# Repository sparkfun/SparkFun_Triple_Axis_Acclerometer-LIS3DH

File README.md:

SparkFun Triple Axis Accelerometer Breakout - LIS3DH (Qwiic)
========================================

<table class="table table-hover table-striped table-bordered">
  <tr align="center">
   <td></td> 
   <td></td>
  </tr>
  <tr align="center">
    <td><a href="https://www.sparkfun.com/sparkfun-triple-axis-accelerometer-breakout-lis3dh.html">SparkFun Triple Axis Accelerometer Breakout - LIS3DH (Qwiic) <br />(SEN-29528)</a></td>
    <td><a href="https://www.sparkfun.com/sparkfun-micro-triple-axis-accelerometer-breakout-lis3dh.html">SparkFun Micro Triple Axis Accelerometer Breakout - LIS3DH (Qwiic) <br />(SEN-29529)</a></td>
  </tr>
</table>

The SparkFun Triple Axis Accelerometer Breakout - LIS3DH (Qwiic) and SparkFun Micro Triple Axis Accelerometer Breakout - LIS3DH (Qwiic) are Qwiic breakouts for the LIS3DH from STMicroelectronics<sup>&trade;</sup>. The LIS3DH is a smart, low-power, three-axis, capacitive micro-machined accelerometer with 12 bits of resolution that you can use to add translation detection to your project. These Qwiic breakouts let users easily and solderlessly integrate a precise 3-axis accelerometer into their project.

Repository Contents
-------------------

* **/Documentation** - Data sheets, additional product information
* **/Hardware** - Eagle design files (.brd, .sch)
* **/Production** - Production panel files (.brd)

Documentation
--------------
* **[Arduino Library](https://github.com/sparkfun/SparkFun_LIS3DH_Arduino_Library)** - Arduino library for the SparkFun LIS3DH Breakouts.
* **[Hookup Guide](https://learn.sparkfun.com/tutorials/lis3dh-hookup-guide)** - Basic hookup guide for the SparkFun LIS3DH Breakouts.

Product Versions
----------------
* [SEN-29528](https://www.sparkfun.com/sparkfun-triple-axis-accelerometer-breakout-lis3dh.html) - Standard 1"x1" Qwiic Breakout
* [SEN-29529](https://www.sparkfun.com/sparkfun-micro-triple-axis-accelerometer-breakout-lis3dh.html) - Micro Qwiic Breakout

License Information
-------------------

This product is _**open source**_! 

Please review the LICENSE.md file for license information. 

If you have any questions or concerns on licensing, please contact technical support on our [SparkFun forums](https://forum.sparkfun.com/viewforum.php?f=152).

Distributed as-is; no warranty is given.

- Your friends at SparkFun.

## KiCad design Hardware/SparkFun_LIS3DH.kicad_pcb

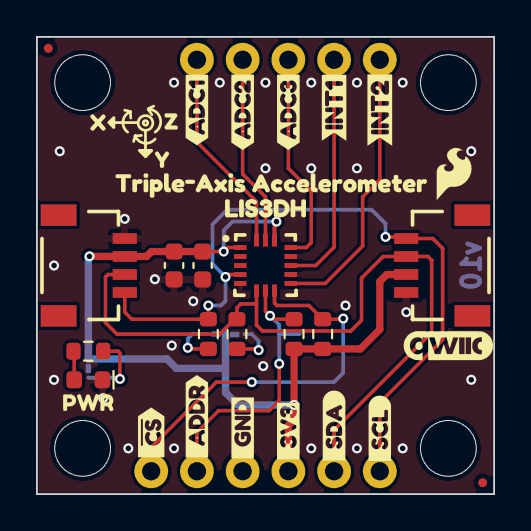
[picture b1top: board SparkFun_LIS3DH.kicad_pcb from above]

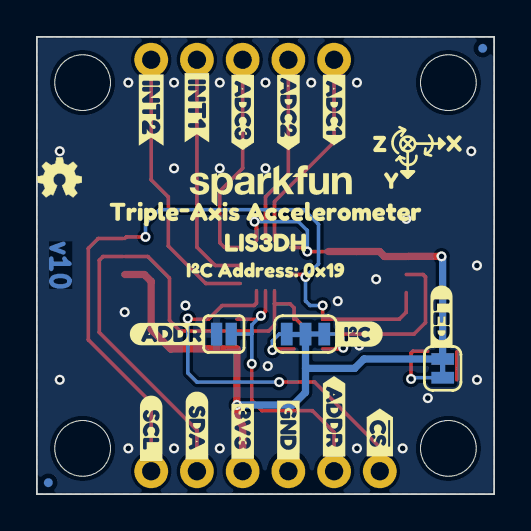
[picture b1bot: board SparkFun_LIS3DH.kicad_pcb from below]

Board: 2 copper layers, 25.4 x 25.4 mm, 64 parts (26 on the bottom side), 15 nets.

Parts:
C1: 10uF; C_0603_1608Metric
C2: 0.1uF; C_0603_1608Metric
D1: Red; LED_0603_1608Metric_Red
FID1, FID2, FID3, FID4: Fiducial_0.5mm; Fiducial_0.5mm_Mask1mm
G4: OSHW_Logo; Creative_Commons_License
J1: Conn_01x02; 1x02
J2: Conn_01x05; 1x05
J3, J5: Qwiic_RA; JST_SMD_1.0mm-4_Black
J4: I2C; 1x04
JP1: LED; Jumper_2_NC_Trace
JP2: I2C; Jumper_3_NC-2_Trace
JP3: ADDR; Jumper_2_NO
R1, R4: 10k; R_0603_1608Metric
R2, R3: 2.2k; R_0603_1608Metric
R5: 4.7k; R_0603_1608Metric
Ref**: Val**; OSHW_Logo_2.5mm
ST1, ST2, ST3, ST4: Standoff
U1: LIS3DH; ST_LGA-16_3x3mm_P0.5mm_5x3
kibuzzard-65A8A8B4: G***; kibuzzard-65A8A8B4
kibuzzard-67D9D97F: G***; kibuzzard-67D9D97F
kibuzzard-685C51A0, kibuzzard-685C51A0#2: G***; kibuzzard-685C51A0
kibuzzard-685C52CC, kibuzzard-685C52CC#2: G***; kibuzzard-685C52CC
kibuzzard-685C52E1, kibuzzard-685C52E1#2: G***; kibuzzard-685C52E1
kibuzzard-685C54A5: G***; kibuzzard-685C54A5
kibuzzard-685C54B5: G***; kibuzzard-685C54B5
kibuzzard-685C54BC: G***; kibuzzard-685C54BC
kibuzzard-685C549D: G***; kibuzzard-685C549D
kibuzzard-6838B6EB: G***; kibuzzard-6838B6EB
kibuzzard-6838B97C: G***; kibuzzard-6838B97C
kibuzzard-6838B744: G***; kibuzzard-6838B744
kibuzzard-6838B970: G***; kibuzzard-6838B970
kibuzzard-6838B976: G***; kibuzzard-6838B976
kibuzzard-6838B980: G***; kibuzzard-6838B980
kibuzzard-6838B984: G***; kibuzzard-6838B984
kibuzzard-6838B988: G***; kibuzzard-6838B988
kibuzzard-6838BA4A: G***; kibuzzard-6838BA4A
kibuzzard-6838BBAA: G***; kibuzzard-6838BBAA
kibuzzard-68376F48: G***; kibuzzard-68376F48
kibuzzard-68376F54: G***; kibuzzard-68376F54
kibuzzard-684892AC: G***; kibuzzard-684892AC
kibuzzard-684892BE: G***; kibuzzard-684892BE
kibuzzard-6837731A: G***; kibuzzard-6837731A
kibuzzard-6848928D: G***; kibuzzard-6848928D
kibuzzard-6848939E: G***; kibuzzard-6848939E
kibuzzard-68377305: G***; kibuzzard-68377305
kibuzzard-68377311: G***; kibuzzard-68377311
kibuzzard-68489282: G***; kibuzzard-68489282
kibuzzard-68489296: G***; kibuzzard-68489296
kibuzzard-68489323: G***; kibuzzard-68489323
kibuzzard-68489388: G***; kibuzzard-68489388
kibuzzard-68489408: G***; kibuzzard-68489408
kibuzzard-68489728: G***; kibuzzard-68489728

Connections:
3.3V: C1.1, C2.1, J3.2, J4.2, J5.2, JP1.2 (B), JP2.2 (B), R1.2, R4.2, U1.1 (VDDIO), U1.14 (VDD)
ADC1: J2.5, U1.16 (ADC1)
ADC2: J2.4, U1.15 (ADC2)
ADC3: J2.3, U1.13 (ADC3)
ADDR/SDO: J1.2, JP3.2 (B), R4.1, U1.7 (SA0/SDO)
GND: C1.2, C2.2, D1.1 (K), J3.1, J4.1, J5.1, JP3.1 (A), U1.5 (GND), U1.10 (RES), U1.12 (GND)
INT1: J2.2, U1.11 (INT1)
INT2: J2.1, U1.9 (INT2)
unnamed: D1.2 (A), R5.1
unnamed: JP1.1 (A), R5.2
unnamed: JP2.1 (A), R3.2
unnamed: JP2.3 (C), R2.2
SCL: J3.4, J4.4, J5.4, R3.1, U1.4 (SCL/SPC)
SDA: J3.3, J4.3, J5.3, R2.1, U1.6 (SDA/SDI)
~CS: J1.1, R1.1, U1.8 (~CS/MODE)

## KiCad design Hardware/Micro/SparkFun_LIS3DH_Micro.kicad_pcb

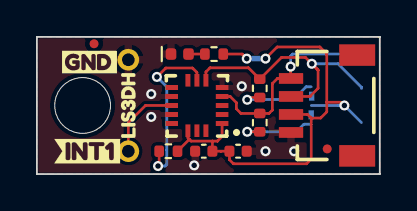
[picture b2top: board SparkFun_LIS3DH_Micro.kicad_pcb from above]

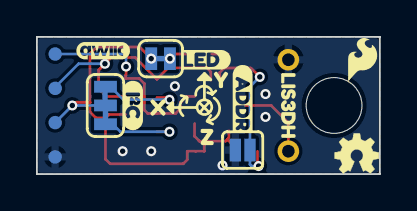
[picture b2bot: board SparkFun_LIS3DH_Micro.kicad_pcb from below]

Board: 2 copper layers, 19.0 x 7.6 mm, 33 parts (15 on the bottom side), 10 nets.

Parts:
C3: 0.1uF; C_0402_1005Metric
C4: 10uF; C_0402_1005Metric
D1: Red; LED_0402_1005Metric_Red
FID3, FID4: Fiducial_0.5mm; Fiducial_0.5mm_Mask1mm
G4: OSHW_Logo; Creative_Commons_License
J1, J5: PTH_1x1mm; 1x01_1x1mm
J2: Qwiic_RA; JST_SMD_1.0mm-4_Black
JP1: LED; Jumper_2_NC_Trace
JP2: I2C; Jumper_3_NC-2_Trace
JP3: ADDR; Jumper_2_NO
R1, R6: 2.2k; R_0402_1005Metric
R2: 10k; R_0402_1005Metric
R3: 4.7k; R_0402_1005Metric
Ref**: Val**; OSHW_Logo_2.5mm
ST1: Standoff
TP5, TP6, TP7, TP8: 0.75mm; TestPoint-0.75mm
U1: LIS3DH; ST_LGA-16_3x3mm_P0.5mm_5x3
kibuzzard-685C51A0: G***; kibuzzard-685C51A0
kibuzzard-685C52CC: G***; kibuzzard-685C52CC
kibuzzard-685C52E1: G***; kibuzzard-685C52E1
kibuzzard-6841DC9E: G***; kibuzzard-6841DC9E
kibuzzard-6841DC10, kibuzzard-6841DC10#2: G***; kibuzzard-6841DC10
kibuzzard-6841DC42: G***; kibuzzard-6841DC42
kibuzzard-6841DC70: G***; kibuzzard-6841DC70
kibuzzard-68489829: G***; kibuzzard-68489829
kibuzzard-68489831: G***; kibuzzard-68489831

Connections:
3.3V: C3.1, C4.1, J2.2, JP1.2 (B), JP2.2 (B), R2.2, TP7.1, U1.1 (VDDIO), U1.14 (VDD)
ADDR/SDO: JP3.2 (B), R2.1, U1.7 (SA0/SDO)
GND: C3.2, C4.2, D1.1 (K), J2.1, J5.1, JP3.1 (A), TP8.1, U1.5 (GND), U1.10 (RES), U1.12 (GND)
INT1: J1.1, U1.11 (INT1)
unnamed: D1.2 (A), R3.2
unnamed: JP1.1 (A), R3.1
unnamed: JP2.1 (A), R6.2
unnamed: JP2.3 (C), R1.2
SCL: J2.4, R6.1, TP5.1, U1.4 (SCL/SPC)
SDA: J2.3, R1.1, TP6.1, U1.6 (SDA/SDI)

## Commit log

2025-05-28 Makes some changes to the main IC
2025-05-28 Adds the new LIS3DH symbol and footprint to schematic and PCB
2025-05-28 Adds silks, moves components arounds
2025-05-29 Adds silk to top
2025-05-29 Adjust routing, adds keepout underneath sensor, moves clock out from underneath IC
2025-05-29 Adjusts schematic so that the connectors have more space
2025-05-29 Aligns the PTH for breadboard-ability
2025-05-29 Moves some net over just a smidge
2025-05-29 Updates design with keepout underneath IC baked into the footprint.
2025-05-30 Finishes schematic for mini sized version
2025-05-30 Gets the correct shape of the Micro
2025-06-03 Adds testpoints
2025-06-05 Adds 0402 Red LED - reroutes the PCB
2025-06-05 Positions the testpoints according to their position in every other micro design
2025-06-05 Adds silk
2025-06-05 Adds more silk and adds measure
2025-06-05 Fixes measures, adjusts some traces
2025-06-09 Repalces "mini" in file names with "micro"
2025-06-09 Fixes design information in title bar
2025-06-10 Fixes some silk
2025-06-10 Fixes LED silk
2025-06-10 Fixes silk on micro, and adds note about 22AWG wire with PTH
2025-06-12 Updates LIS3DH according to new changes
2025-06-12 Updates LIS3DH in the micro board according to new changes
2025-06-12 Updates the 1 mm PTH part
2025-06-25 Addes axes to the IU
2025-06-25 Moves v10 in board, updates IC symbol, and fixes various text
2025-06-25 Adds axes to design
2025-06-26 Small adjustment to the axis silk
2025-06-26 Removes gyroscopic arrows from silk - this is an accelerometer 😝
2025-06-27 Moves the 1x1 to it's own folder
2025-07-22 Update README.md
    Update readme from template.

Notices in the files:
parts and their libraries:
https://creativecommons.org/licenses/by-sa/4.0
Released under the Creative Commons Attribution Share-Alike 4.0 License
